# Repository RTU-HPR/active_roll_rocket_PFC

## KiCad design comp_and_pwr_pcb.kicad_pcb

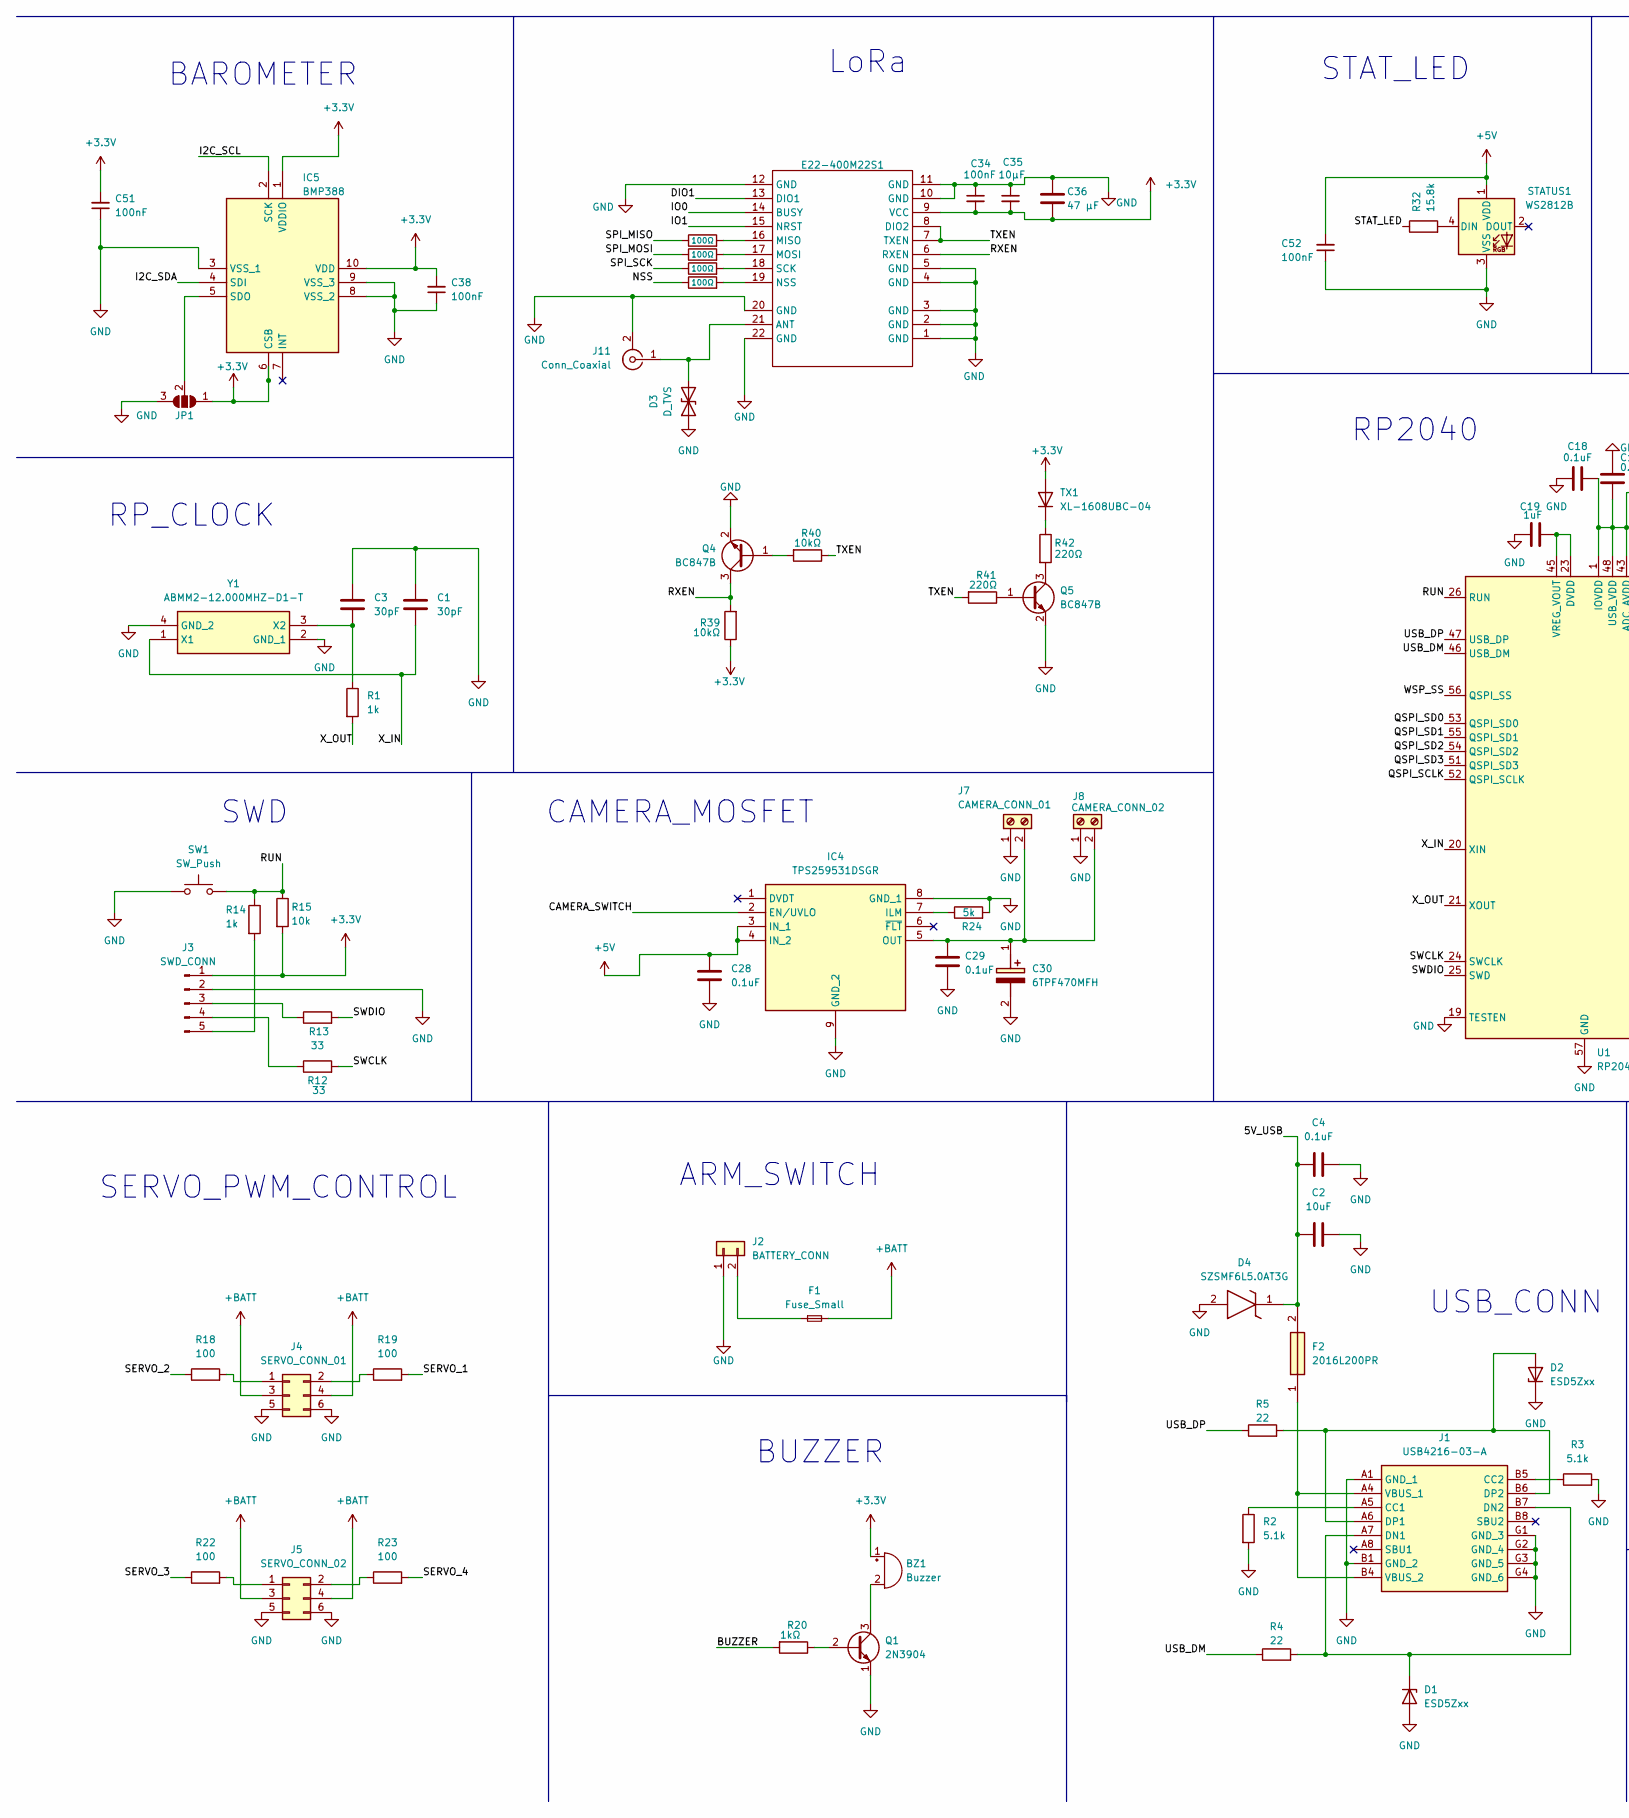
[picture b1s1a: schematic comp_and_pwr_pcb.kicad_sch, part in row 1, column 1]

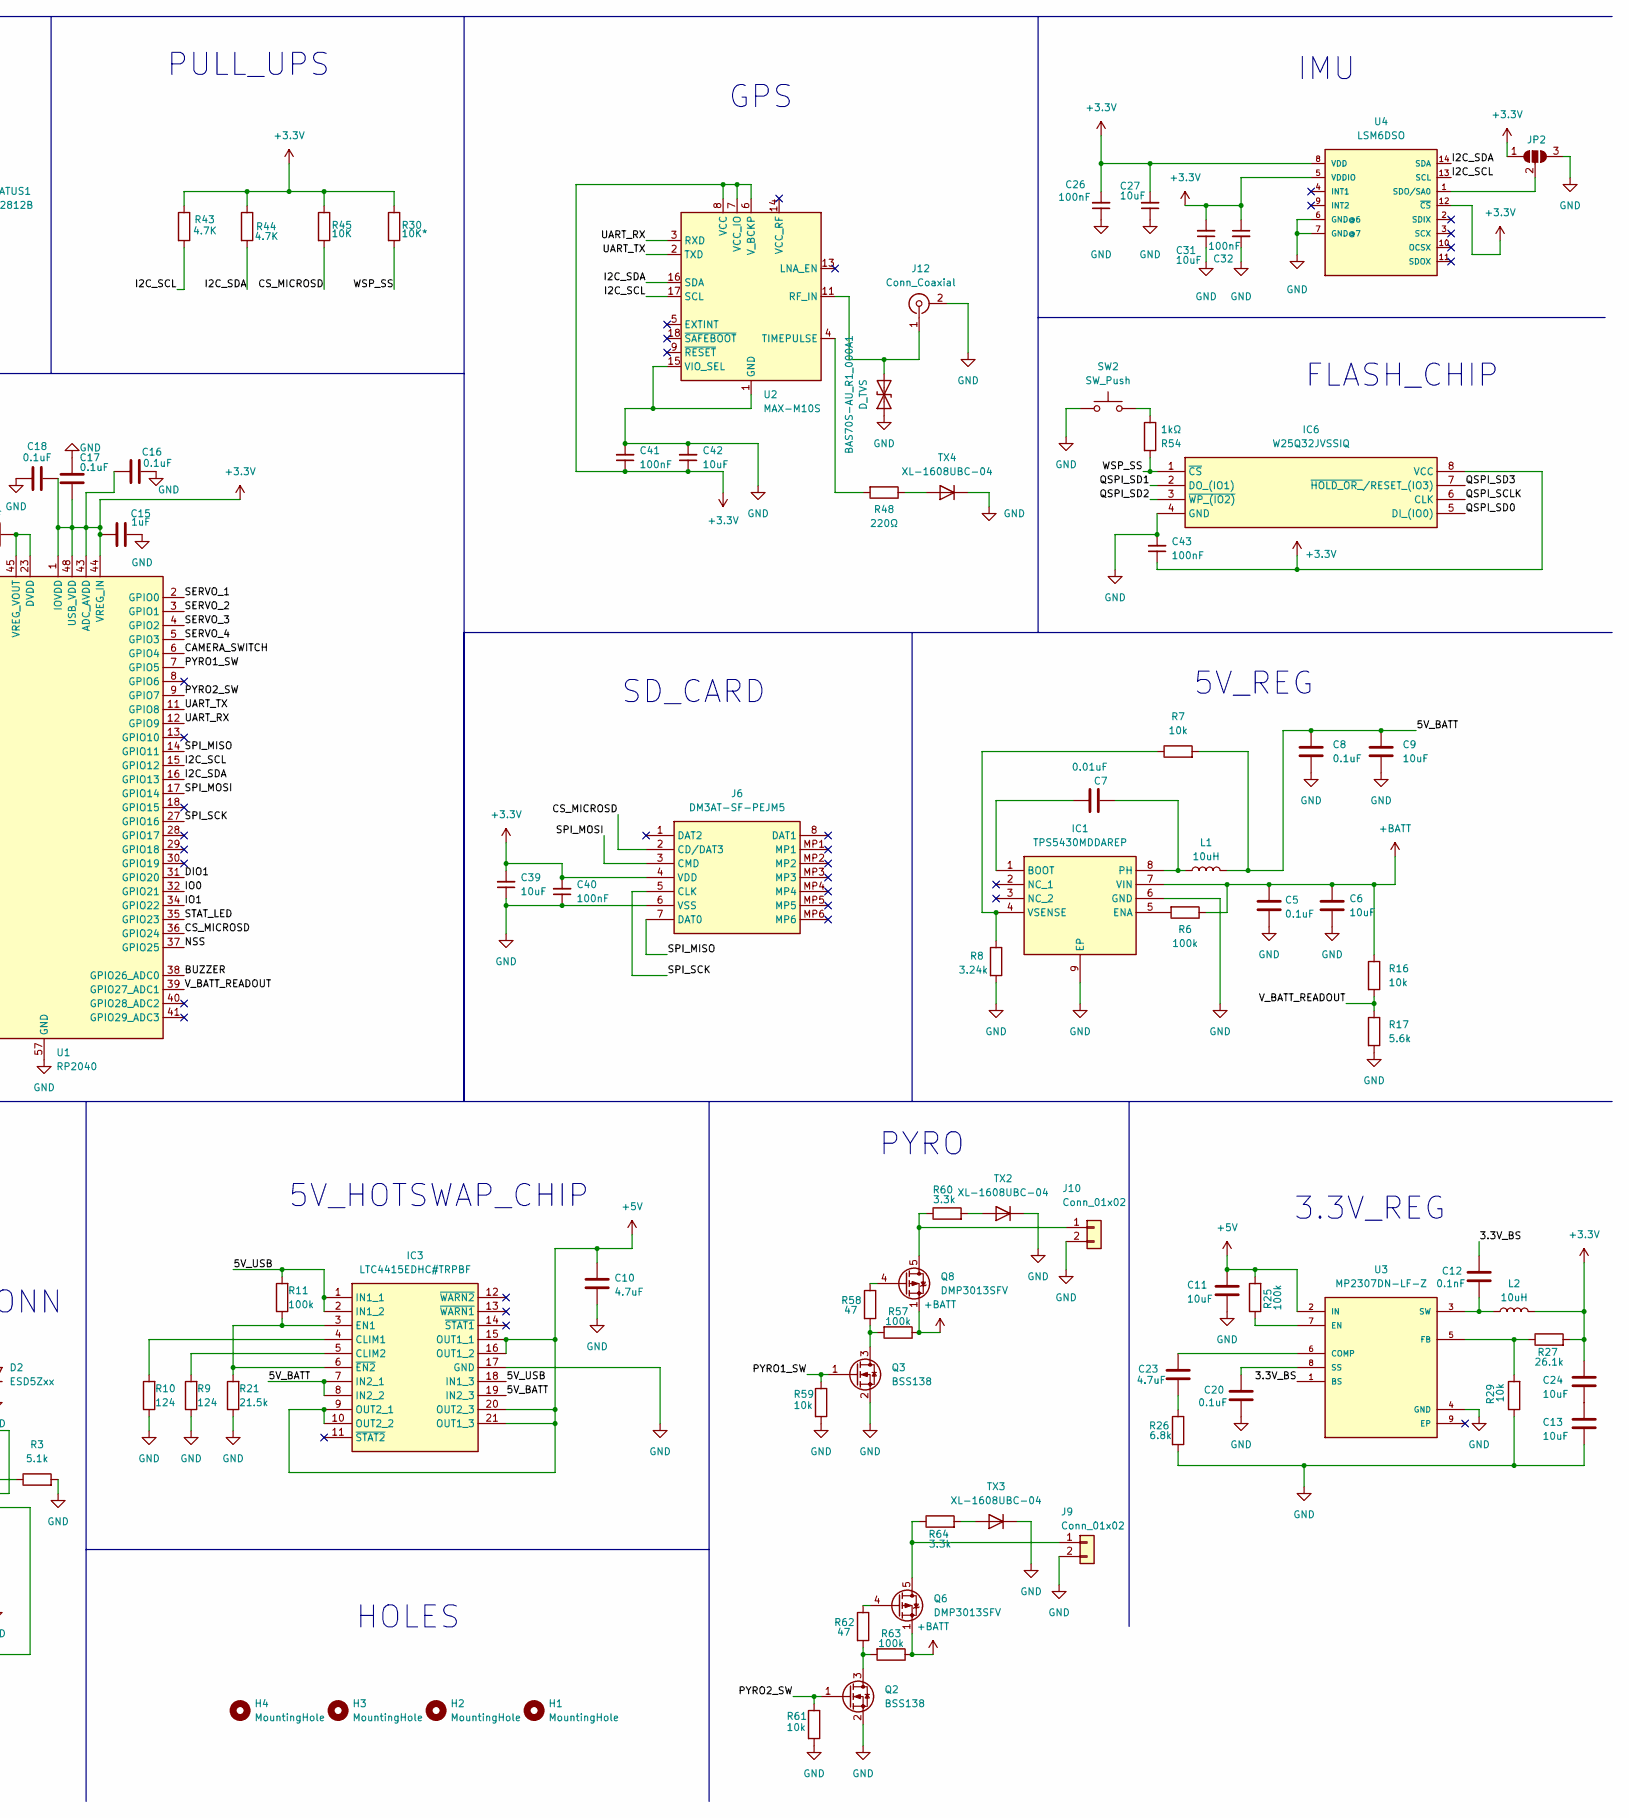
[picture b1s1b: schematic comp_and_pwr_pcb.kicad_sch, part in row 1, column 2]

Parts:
BAS70S-AU_R1_000A1: D_TVS; D_SOD-523; MPN BAS70S-AU_R1_000A1
BZ1: Buzzer; Buzzer_CUI_CPT-9019S-SMT; MPN CPT-9019S-SMT-TR
C1, C3: 30pF; C_0402_1005Metric; MPN C0402C300F5GAC
C2, C11, C13, C24, C39: 10uF; C_1206_3216Metric; MPN C0402C106M9PACTU
C4, C5, C8, C16, C17, C18, C20, C28, C29: 0.1uF; C_0402_1005Metric; MPN C0402C104K4RAC7411
C6, C9, C42: 10uF; C_0603_1608Metric; MPN C0402C106M9PACTU
C7: 0.01uF; C_0402_1005Metric; MPN GRM1555C1H101FA01D
C10: 4.7uF; C_0402_1005Metric; MPN C0805C475K8PACTU
C12: 0.1nF; C_0402_1005Metric; MPN C0402C104K4RAC7411
C15, C19: 1uF; C_0402_1005Metric; MPN C0402C105K8PACTU
C23: 4.7uF; C_0603_1608Metric; MPN C0805C475K8PACTU
C26, C32, C34, C38, C40, C41, C43, C52: 100nF; C_0402_1005Metric; MPN C0402C104K4RAC7411
C27, C31: 10uF; C_0402_1005Metric; MPN C0402C106M9PACTU
C30: 6TPF470MFH; Mouser Part Number 667-6TPF470MFH
C35: 10µF; C_0402_1005Metric; MPN C0402C106M9PACTU
C36: 47 µF; C_1206_3216Metric; MPN T495X476K020AHE150
C51: 100nF; C_0402_1005Metric; MPN KEMET
D1, D2: ESD5Zxx; D_SOD-523; MPN ESD5Z5.0T1G
D3: D_TVS; D_SOD-523; MPN BAS70S-AU_R1_000A1
D4: SZSMF6L5.0AT3G; SMFA2005CA; Manufacturer_Part_Number SZSMF6L5.0AT3G
E22-400M22S1: E22-400M22S
F1: Fuse_Small; Fuse_0402_1005Metric; MPN 0ABA-1000-TN
F2: 2016L200PR; Fuse_0805_2012Metric; Mouser Part Number 576-2016L200PR
H1, H2, H3, H4: MountingHole; MountingHole_3.2mm_M3
IC1: TPS5430MDDAREP; SOIC127P600X170-9N; Mouser Part Number 595-TPS5430MDDAREP
IC3: LTC4415EDHC#TRPBF; DFN-18-1EP_3x5mm_P0.5mm_EP1.66x4.4mm; Mouser Part Number 584-LTC4415EDHCTRPBF
IC4: TPS259531DSGR; SON50P200X200X80-9N; Mouser Part Number 595-TPS259531DSGR
IC5: BMP388; Manufacturer_Part_Number BMP388
IC6: W25Q32JVSSIQ; SOIC127P790X216-8N; Manufacturer_Part_Number W25Q32JVSSIQ; Mouser Part Number 454-W25Q32JVSSIQ
J1: USB4216-03-A; USB421603A; Mouser Part Number 640-USB4216-03-A
J2: BATTERY_CONN; TerminalBlock_4Ucon_1x02_P3.50mm_Vertical; MPN 284514-2
J3: SWD_CONN; PinHeader_1x05_P2.54mm_Vertical; MPN M20-9990546
J4: SERVO_CONN_01; PinHeader_2x03_P2.54mm_Vertical; MPN 90131-0763
J5: SERVO_CONN_02; PinHeader_2x03_P2.54mm_Vertical; MPN 90131-0763
J6: DM3AT-SF-PEJM5; DM3ATSFPEJM5; Manufacturer_Part_Number DM3AT-SF-PEJM5; Mouser Part Number 798-DM3AT-SF-PEJM5
J7: CAMERA_CONN_01; TerminalBlock_4Ucon_1x02_P3.50mm_Vertical; MPN 284514-2
J8: CAMERA_CONN_02; TerminalBlock_4Ucon_1x02_P3.50mm_Vertical; MPN 284514-2
J9, J10: Conn_01x02; TerminalBlock_4Ucon_1x02_P3.50mm_Vertical; MPN 284514-2
J11, J12: Conn_Coaxial; SMA_Molex_73251-2200_Horizontal; MPN 73251-2200
JP1, JP2: SolderJumper_3_Open; SolderJumper-3_P1.3mm_Open_Pad1.0x1.5mm
L1, L2: 10uH; L_6.3x6.3_H3; MPN 74437349033
Q1: 2N3904; SOT-23; MPN MMBT3904
Q2, Q3: BSS138; SOT-23; MPN BSS138
Q4, Q5: BC847B; SOT-23; MPN BC847B
Q6, Q8: DMP3013SFV; Diodes_PowerDI3333-8; MPN DMP3013SFV-7
R1, R14: 1k; R_0402_1005Metric; MPN RC0402FR‑071KL
R2, R3: 5.1k; R_0402_1005Metric; MPN RC0402FR-075K1L
R4, R5: 22; R_0402_1005Metric; MPN RC0402FR-0722RL
R6, R11, R25, R57, R63: 100k; R_0402_1005Metric; MPN RC0402FR-07100KL
R7, R15, R16, R29, R59, R61: 10k; R_0402_1005Metric; MPN RC0402FR-0710KL
R8: 3.24k; R_0402_1005Metric; MPN RC0402FR-073R24L
R9, R10: 124; R_0402_1005Metric; MPN RC0402FR-07124RL
R12, R13: 33; R_0402_1005Metric; MPN RC0402JR-7D33RL
R17: 5.6k; R_0402_1005Metric; MPN RC0402FR-075K6L
R18: 100; R_0402_1005Metric
R19, R22, R23: 100; R_0402_1005Metric; MPN RC1206FR-07100RL
R20: 1kΩ; R_0402_1005Metric; MPN RC0402FR‑071KL
R21: 21.5k; R_0402_1005Metric; MPN RC0402FR-0721K5L
R24: 5k; R_0402_1005Metric; MPN RC0402FR-075K76L
R26: 6.8k; R_0402_1005Metric; MPN RC0402FR-076K8L
R27: 26.1k; R_0402_1005Metric; MPN RC0402FR-0726K1L
R30: 10K*; R_0402_1005Metric; MPN RC0402FR-0710KL
R32: 15.8k; R_0402_1005Metric; MPN RC0603FR-0715K8L
R35, R36, R37, R38: 100Ω; R_0402_1005Metric; MPN RC0402FR-07100RL
R39, R40: 10kΩ; R_0402_1005Metric; MPN RC0402FR-0710KL
R41, R42: 220Ω; R_0402_1005Metric; MPN RC0402FR-07220R
R43, R44: 4.7K; R_0402_1005Metric; MPN RC0402FR-074K7L
R45: 10K; R_0402_1005Metric; MPN RC0402FR-0710KL
R48: 220Ω; R_0402_1005Metric; MPN RC0402FR-07220RL
R54: 1kΩ; R_0402_1005Metric; MPN RC0402FR-071KL
R58, R62: 47; R_0402_1005Metric; MPN RC0402FR-0747RL
R60, R64: 3.3k; R_0402_1005Metric; MPN RC0402FR-073K3L
STATUS1: WS2812B; MPN COM-24837
SW1, SW2: SW_Push; SW_SPST_PTS645Sx43SMTR92; MPN PTS645SM43SMTR92
TX1, TX2, TX3, TX4: XL-1608UBC-04; LED_0603_1608Metric; MPN XL-1608UBC-04
U1: RP2040; QFN-56-1EP_7x7mm_P0.4mm_EP3.2x3.2mm; MPN RP2040
U2: MAX-M10S; MAXM10M00B; MPN MAX-M10S-00B
U3: MP2307DN-LF-Z; SOIC127P600X170-9N; PARTREV 1.9
U4: LSM6DSO; LGA14L; MPN LSM6DSOTR
Y1: ABMM2-12.000MHZ-D1-T; ABMM2; Mouser Part Number 815-ABMM212000MHZD1T

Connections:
+5V: C10.1, C11.1, C28.1, C52.2, IC3.9 (OUT2_1), IC3.10 (OUT2_2), IC3.15 (OUT1_1), IC3.16 (OUT1_2), IC3.20 (OUT2_3), IC3.21 (OUT1_3), IC4.3 (IN_1), IC4.4 (IN_2), R25.2, STATUS1.1 (VDD), U3.2 (IN)
+BATT: C5.1, C6.1, F1.2, IC1.7 (VIN), J4.3, J4.4, J5.3, J5.4, Q6.1 (S), Q6.2 (S), Q6.3 (S), Q8.1 (S), Q8.2 (S), Q8.3 (S), R6.1, R16.1, R57.1, R63.1
/3.3V_BS: C12.1, U3.1 (BS)
/5V_BATT: C8.2, C9.2, IC3.7 (IN2_1), IC3.8 (IN2_2), IC3.19 (IN2_3), L1.2, R7.2
/BUZZER: R20.2, U1.38 (GPIO26_ADC0)
/CAMERA_SWITCH: IC4.2 (EN/UVLO), U1.6 (GPIO4)
/CS_MICROSD: J6.2 (CD/DAT3), R45.2, U1.36 (GPIO24)
/DIO1: E22-400M22S1.13 (DIO1), U1.31 (GPIO20)
/I2C_SDA: IC5.4 (SDI), R44.2, U1.16 (GPIO13), U2.16 (SDA), U4.14 (SDA)
/IO0: E22-400M22S1.14 (BUSY), U1.32 (GPIO21)
/IO1: E22-400M22S1.15 (NRST), U1.34 (GPIO22)
/NSS: R38.1, U1.37 (GPIO25)
/PYRO1_SW: Q3.1 (G), R59.1, U1.7 (GPIO5)
/PYRO2_SW: Q2.1 (G), R61.1, U1.9 (GPIO7)
/QSPI_SCLK: IC6.6 (CLK), U1.52 (QSPI_SCLK)
/QSPI_SD0: IC6.5 (DI_(IO0)), U1.53 (QSPI_SD0)
/QSPI_SD1: IC6.2 (DO_(IO1)), U1.55 (QSPI_SD1)
/QSPI_SD2: IC6.3 (~WP_(IO2)), U1.54 (QSPI_SD2)
/QSPI_SD3: IC6.7 (~HOLD_OR_/RESET_(IO3)), U1.51 (QSPI_SD3)
/RUN: R14.1, R15.1, SW1.2, U1.26 (RUN)
/RXEN: E22-400M22S1.6 (RXEN), Q4.3 (C), R39.2
/SERVO_1: R19.2, U1.2 (GPIO0)
/SERVO_2: R18.1, U1.3 (GPIO1)
/SERVO_3: R22.1, U1.4 (GPIO2)
/SERVO_4: R23.2, U1.5 (GPIO3)
/SPI_MISO: J6.7 (DAT0), R35.1, U1.14 (GPIO11)
/SPI_MOSI: J6.3 (CMD), R36.1, U1.17 (GPIO14)
/SPI_SCK: J6.5 (CLK), R37.1, U1.27 (GPIO16)
/STAT_LED: R32.1, U1.35 (GPIO23)
/SWCLK: R12.2, U1.24 (SWCLK)
/SWDIO: R13.2, U1.25 (SWD)
/TXEN: E22-400M22S1.7 (TXEN), E22-400M22S1.8 (DIO2), R40.1, R41.2
/UART_RX: U1.12 (GPIO9), U2.3 (RXD)
/UART_TX: U1.11 (GPIO8), U2.2 (TXD)
/USB_DM: R4.1, U1.46 (USB_DM)
/USB_DP: R5.1, U1.47 (USB_DP)
/V_BATT_READOUT: R16.2, R17.1, U1.39 (GPIO27_ADC1)
/WSP_SS: IC6.1 (~CS), R30.2, R54.2, U1.56 (QSPI_SS)
/X_IN: C1.1, U1.20 (XIN), Y1.1 (X1)
/X_OUT: R1.2, U1.21 (XOUT)
unnamed: BZ1.2 (-), Q1.3 (C)
unnamed: C13.1, C24.2
unnamed: C23.2, R26.1
unnamed: C29.1, C30.1 (+), IC4.5 (OUT), J7.2, J8.2
unnamed: D1.1 (K), J1.A7 (DN1), J1.B7 (DN2), R4.2
unnamed: D2.2 (A), J1.A6 (DP1), J1.B6 (DP2), R5.2
unnamed 46: BAS70S-AU_R1_000A1.2 (A2), J12.1 (In), U2.11 (RF_IN); also elsewhere on the board
unnamed: E22-400M22S1.16 (MISO), R35.2
unnamed: E22-400M22S1.17 (MOSI), R36.2
unnamed: E22-400M22S1.19 (NSS), R38.2
unnamed: E22-400M22S1.18 (SCK), R37.2
unnamed: C7.1, IC1.1 (BOOT)
unnamed: IC1.5 (ENA), R6.2
unnamed: C7.2, IC1.8 (PH), L1.1
unnamed: IC1.4 (VSENSE), R7.1, R8.1
unnamed: IC3.4 (CLIM1), R10.2
unnamed: IC5.5 (SDO), JP1.2 (C)
unnamed: J1.A5 (CC1), R2.1
unnamed: J1.B5 (CC2), R3.1
unnamed: F2.1, J1.A4 (VBUS_1), J1.B4 (VBUS_2)
unnamed: F1.1, J2.2
unnamed: J3.3, R13.1
unnamed: J3.4, R12.1
unnamed: J3.5, R14.2
unnamed: J4.1, R18.2
unnamed: J4.2, R19.1
unnamed: J5.1, R22.2
unnamed: J5.2, R23.1
unnamed: J9.1, Q6.5 (D), R64.1
unnamed: J10.1, Q8.5 (D), R60.1
unnamed: JP2.2 (C), U4.1 (SDO/SA0)
unnamed: Q1.2 (B), R20.1
unnamed: Q2.3 (D), R62.2, R63.2
unnamed: Q3.3 (D), R57.2, R58.2
unnamed: Q4.1 (B), R40.2
unnamed: Q5.1 (B), R41.1
unnamed: Q5.3 (C), R42.2
unnamed: Q6.4 (G), R62.1
unnamed: Q8.4 (G), R58.1
unnamed: R54.1, SW2.2
unnamed: R32.2, STATUS1.4 (DIN)
unnamed: R42.1, TX1.1 (K)
unnamed: R60.2, TX2.2 (A)
unnamed: R64.2, TX3.2 (A)
unnamed: R48.1, TX4.2 (A)
unnamed: C19.2, U1.23 (DVDD), U1.45 (VREG_VOUT), U1.50 (DVDD)
unnamed: R48.2, U2.4 (TIMEPULSE)
unnamed: C23.1, U3.6 (COMP)
unnamed: R25.1, U3.7 (EN)
unnamed: R27.1, R29.2, U3.5 (FB)
unnamed: C20.1, U3.8 (SS)
unnamed: C12.2, L2.1, U3.3 (SW)
unnamed: C3.1, R1.1, Y1.3 (X2)
RF_NET: D3.2 (A2), E22-400M22S1.21 (ANT), J11.1 (In)

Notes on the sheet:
USB_CONN
5V_REG
RP2040
SD_CARD
5V_HOTSWAP_CHIP
SERVO_PWM_CONTROL
IMU
PULL_UPS
FLASH_CHIP
LoRa
BUZZER
RP_CLOCK
HOLES
GPS
BAROMETER
SWD
CAMERA_MOSFET
3.3V_REG
PYRO
ARM_SWITCH
STAT_LED

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
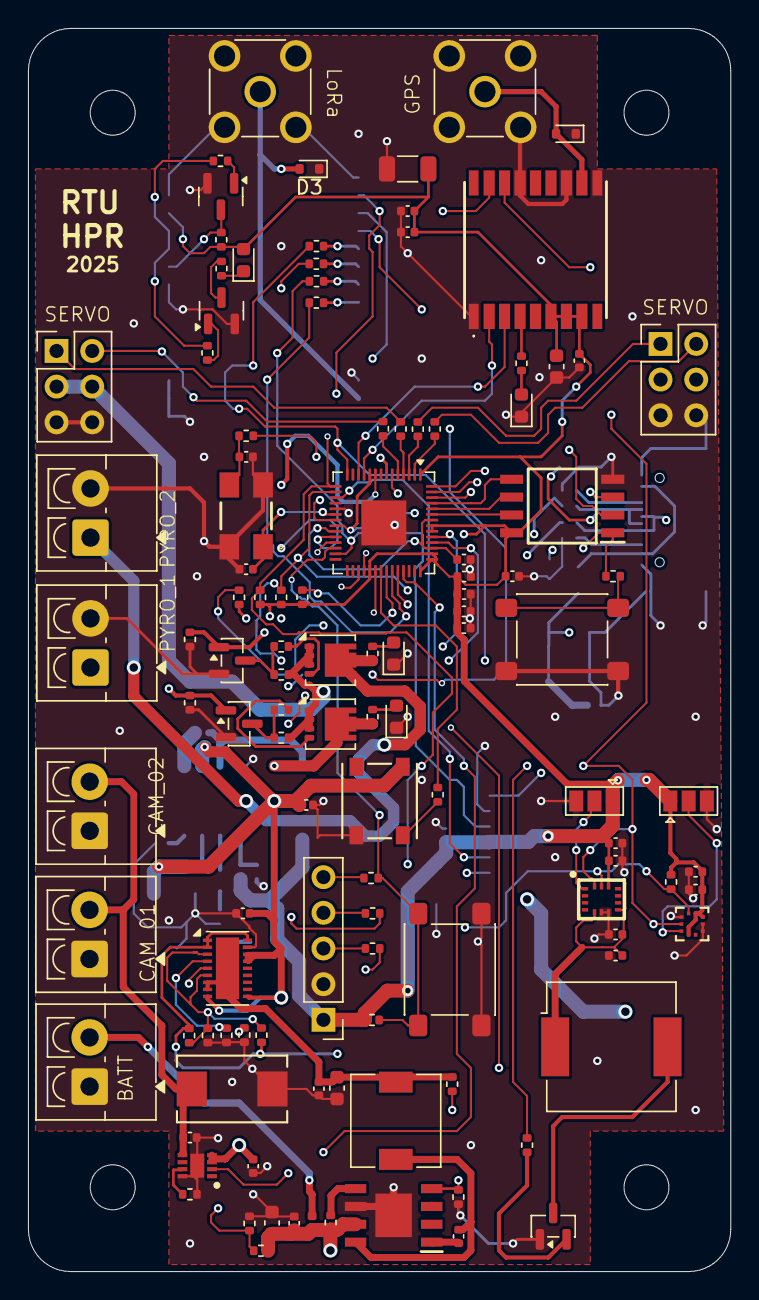
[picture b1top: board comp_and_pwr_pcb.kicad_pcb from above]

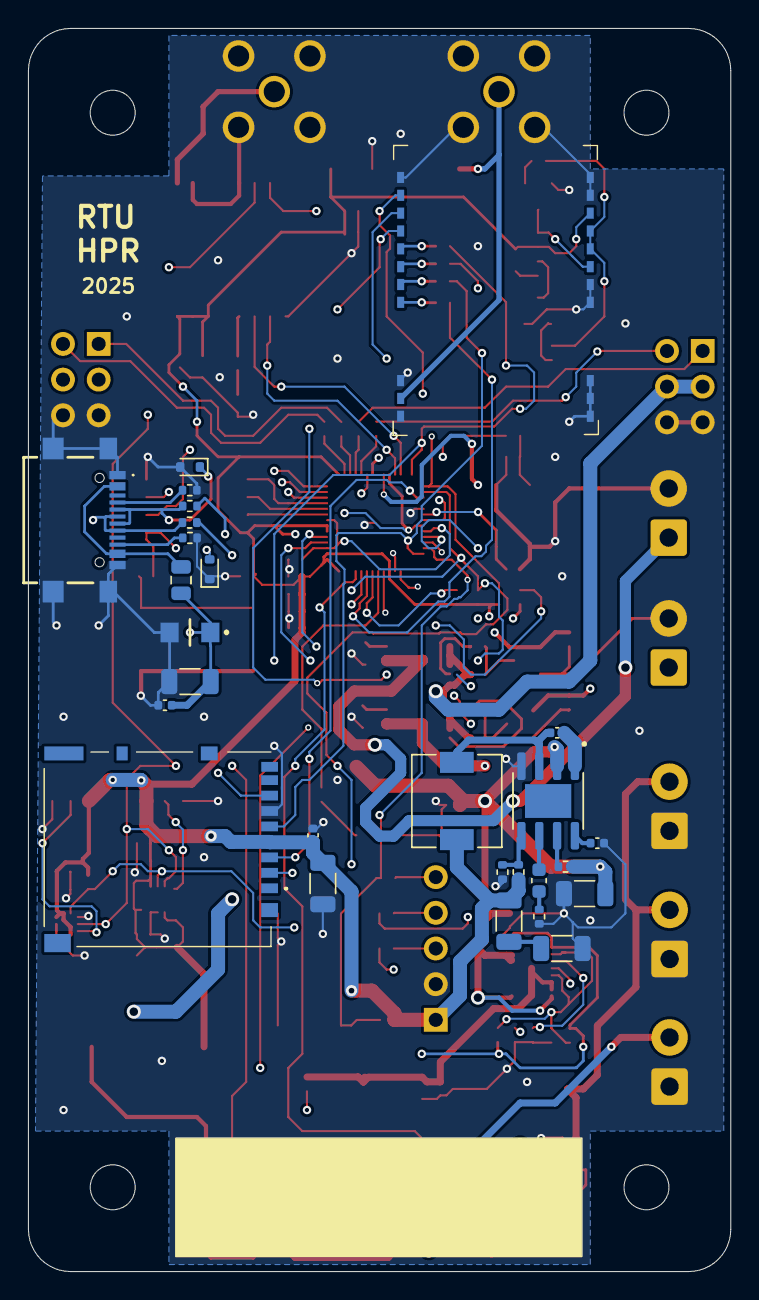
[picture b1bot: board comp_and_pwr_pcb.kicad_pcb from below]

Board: 4 copper layers, 50.0 x 88.5 mm, 145 parts (27 on the bottom side), 101 nets.

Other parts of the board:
D5: D_TVS; D_SOD-523
R9#2: 124; R_0402_1005Metric
R24#2: 5k; R_0402_1005Metric

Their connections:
unnamed 46: D5.2 (A2); also elsewhere on the board

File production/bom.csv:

Designator,Footprint,Quantity,Value,LCSC Part #
BZ1,Buzzer_CUI_CPT-9019S-SMT,1,Buzzer,
"C1, C3",0402,2,30pF,
C10,0402,1,4.7uF,
"C11, C13, C2, C24, C39",1206,5,10uF,
C12,0402,1,0.1nF,
"C15, C19",0402,2,1uF,
"C16, C17, C18, C20, C28, C29, C4, C5, C8",0402,9,0.1uF,
C23,0603,1,4.7uF,
"C26, C32, C34, C38, C40, C41, C43, C51, C52",0402,9,100nF,
"C27, C31",0402,2,10uF,
C30,6TPF470MFH,1,6TPF470MFH,
C35,0402,1,10µF,
C36,1206,1,47 µF,
"C42, C6, C9",0603,3,10uF,
C7,0402,1,0.01uF,
"D1, D2",D_SOD-523,2,ESD5Zxx,
"D3, D5",D_SOD-523,2,D_TVS,
D4,SMFA2005CA,1,SZSMF6L5.0AT3G,
E22-400M22S1,E22-400M22S,1,~,
F1,0402,1,Fuse_Small,
F2,0805,1,2016L200PR,
IC1,SOIC127P600X170-9N,1,TPS5430MDDAREP,
IC3,DFN-18-1EP_3x5mm_P0.5mm_EP1.66x4.4mm,1,LTC4415EDHC#TRPBF,
IC4,SON50P200X200X80-9N,1,TPS259531DSGR,
IC5,BMP388,1,BMP388,
IC6,SOIC127P790X216-8N,1,W25Q32JVSSIQ,
J1,USB421603A,1,USB4216-03-A,
"J10, J9",TerminalBlock_4Ucon_1x02_P3.50mm_Vertical,2,Conn_01x02,
"J11, J12",SMA_Molex_73251-2200_Horizontal,2,Conn_Coaxial,
J2,TerminalBlock_4Ucon_1x02_P3.50mm_Vertical,1,BATTERY_CONN,
J3,PinHeader_1x05_P2.54mm_Vertical,1,SWD_CONN,
J4,PinHeader_2x03_P2.54mm_Vertical,1,SERVO_CONN_01,
J5,PinHeader_2x03_P2.54mm_Vertical,1,SERVO_CONN_02,
J6,DM3ATSFPEJM5,1,DM3AT-SF-PEJM5,
J7,TerminalBlock_4Ucon_1x02_P3.50mm_Vertical,1,CAMERA_CONN_01,
J8,TerminalBlock_4Ucon_1x02_P3.50mm_Vertical,1,CAMERA_CONN_02,
"L1, L2",L_6.3x6.3_H3,2,10uH,
Q1,SOT-23,1,2N3904,
"Q2, Q3",SOT-23,2,BSS138,
"Q4, Q5",SOT-23,2,BC847B,
"Q6, Q8",Diodes_PowerDI3333-8,2,DMP3013SFV,
"R1, R14",0402,2,1k,
"R10, R9",0402,2,124,
"R11, R25, R57, R6, R63",0402,5,100k,
"R12, R13",0402,2,33,
"R15, R16, R29, R45, R59, R61, R7",0402,7,10k,
R17,0402,1,5.6k,
"R18, R19, R22, R23",0402,4,100,
"R2, R3",0402,2,5.1k,
"R20, R54",0402,2,1kΩ,
R21,0402,1,21.5k,
R24_2,0402,1,4.7kΩ,
R24,0402,1,5k,
R26,0402,1,6.8k,
R27,0402,1,26.1k,
R30,0402,1,10K*,
R32,0402,1,15.8k,
"R35, R36, R37, R38",0402,4,100Ω,
"R39, R40",0402,2,10kΩ,
"R4, R5",0402,2,22,
"R41, R42, R48",0402,3,220Ω,
"R43, R44",0402,2,4.7K,
"R58, R62",0402,2,47,
"R60, R64",0402,2,3.3k,
R8,0402,1,3.24k,
R9_2,0402,1,47k,
STATUS1,WS2812B,1,WS2812B,
"SW1, SW2",SW_SPST_PTS645Sx43SMTR92,2,SW_Push,
"TX1, TX2, TX3, TX4",0603,4,XL-1608UBC-04,
U1,QFN-56-1EP_7x7mm_P0.4mm_EP3.2x3.2mm,1,RP2040,
U2,MAXM10M00B,1,MAX-M10S,
U3,SOIC127P600X170-9N,1,MP2307DN-LF-Z,
U4,LGA14L,1,LSM6DSO,
Y1,ABMM2,1,ABMM2-12.000MHZ-D1-T,

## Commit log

2025-11-11 Initial commit - add KiCad project
2025-11-11 Add KiCad schematic and PCB files for active roll rocket PFC
2025-11-12 Create READ ME
2025-11-12 Add temp.md with initial content
    aaa
2025-11-17 Footprints added and layout finished
2025-11-17 Update: footprints are now assigned to project
2025-11-23 Layout design changing
2025-11-23 Replaced files and updated project
2025-11-26 Initial KiCad project commit
2025-12-02 pfc mistakes fixed
2025-12-02 Just a commit
2025-12-02 Final commit?
2025-12-03 R28 deleted
2025-12-03 Pyro mosfet change
2025-12-03 TVS diodes fixed
2025-12-04 added MPN and manufacturer
2025-12-07 Silkscreen added
2025-12-08 Last update, hopefully
2025-12-10 Production files
